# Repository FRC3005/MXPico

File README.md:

# MXPico
MXP Board for using the Pi Pico I2C with the RoboRIO

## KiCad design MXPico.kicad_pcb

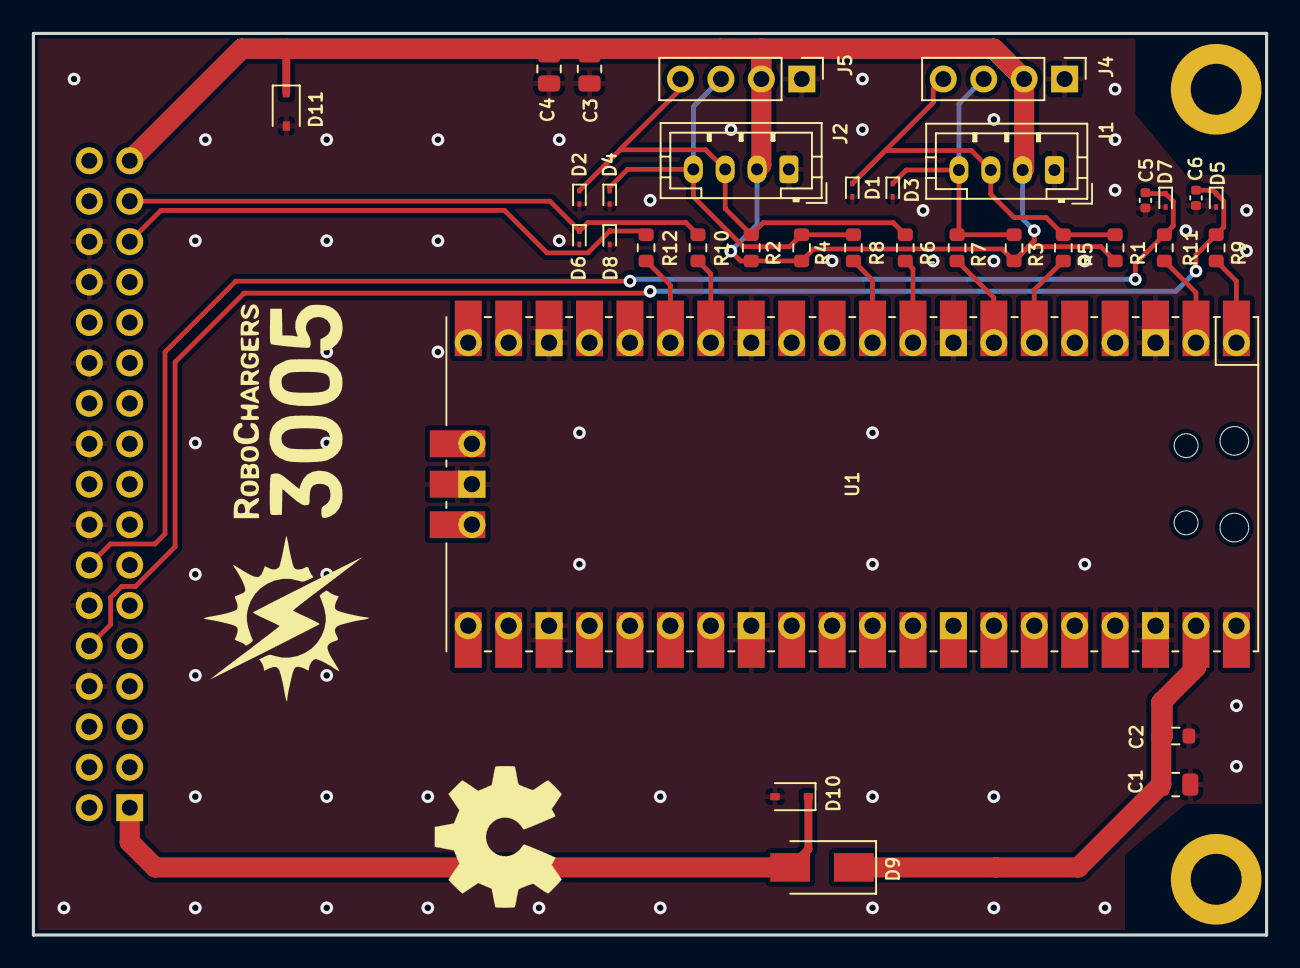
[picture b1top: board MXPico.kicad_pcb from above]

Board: 2 copper layers, 77.5 x 56.6 mm, 37 parts (1 on the bottom side), 20 nets.

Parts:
C1, C3, C4: 10uF; R_0805_2012Metric
C2: 0.1uF; R_0603_1608Metric
C5, C6: 100pF; C_0402_1005Metric
D1, D2, D3, D4, D5, D6, D7, D8: ESD9B3.3ST5G; D_SOD-923
D9: D_Schottky; D_SMA
D10, D11: TVS; D_SOD-323
H1, H2: MountingHole; MountingHole_3.2mm_M3_ISO7380_Pad
J1, J2: JST PH 4-pin; JST_PH_B4B-PH-K_1x04_P2.00mm_Vertical
J3: SH2-34G-P; PinSocket_2x17_P2.54mm_Vertical
J4, J5: 100mil Header; PinHeader_1x04_P2.54mm_Vertical
R1, R2, R3, R4: 4.7k; R_0603_1608Metric
R5, R6, R7, R8, R9, R10, R11, R12: 100; R_0603_1608Metric
U1: Pico; RPi_Pico_SMD_TH

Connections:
+3V3: C3.1, C4.1, D11.1 (K), J1.2, J2.2, J3.33, J4.2, J5.2, R1.1, R2.1, R3.1, R4.1
+5V: D9.2 (A), D10.1 (K), J3.1
/PICO_RX: C5.1, D7.1 (A1), J3.14, R11.2
/PICO_TX: C6.1, D5.1 (A1), J3.10, R9.1
/PULSE0: D6.1 (A1), J3.31, R10.1
/PULSE1: D8.1 (A1), J3.29, R12.2
/SCL0: R7.1, U1.7 (GPIO5)
/SCL1: R8.1, U1.10 (GPIO7)
/SDA0: R5.2, U1.6 (GPIO4)
/SDA1: R6.2, U1.9 (GPIO6)
GND: C1.2, C2.2, C3.2, C4.2, C5.2, C6.2, D1.2 (A2), D2.2 (A2), D3.2 (A2), D4.2 (A2), D5.2 (A2), D6.2 (A2), D7.2 (A2), D8.2 (A2), D10.2 (A), D11.2 (A), J1.1, J2.1, J3.8, J3.12, J3.16, J3.20, J3.24, J3.28, J3.30, J4.1, J5.1, U1.3 (GND), U1.8 (GND), U1.13 (GND), U1.18 (GND), U1.23 (GND), U1.28 (GND), U1.38 (GND), U1.42 (GND)
unnamed: C1.1, C2.1, D9.1 (K), U1.39 (VSYS)
unnamed: D1.1 (A1), J1.3, J4.4, R1.2, R5.1
unnamed: D2.1 (A1), J2.3, J5.4, R2.2, R6.1
unnamed: D3.1 (A1), J1.4, J4.3, R3.2, R7.2
unnamed: D4.1 (A1), J2.4, J5.3, R4.2, R8.2
unnamed: R9.2, U1.1 (GPIO0)
unnamed: R10.2, U1.14 (GPIO10)
unnamed: R11.1, U1.2 (GPIO1)
unnamed: R12.1, U1.15 (GPIO11)

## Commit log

2022-03-22 Initial commit of schematic
2022-03-22 Adds +3.3V from MXP port and zeners
2022-03-23 Adds initial layout and fab files for E1
2022-03-23 Adds manufacturing outputs in .pdf
2022-03-24 Update schematic
